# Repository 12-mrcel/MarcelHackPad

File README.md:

# MarcelHackPad
This is the repository for my HackPad Project, which is aptly named "Marcel Hack Pad"
It is a useful hackpad with a rotary encoder, allowing for some extra buttons and functionality when working on my computer.

The design is inspired by the Apollo mission control desks at NASA, I have used several images as inspiration and reference for design choices. This includes: 

1. The color palette (cream and turqouise)
1. The keycap colors 
1. The triangular name plate _"Flight Director"_ (inspired by a real photo!)
1. The NASA logo on a panel on the side

(this is one of the inspirations!)

See it the project here On KiCanvas: 

## Features of the Project:

1. **Six** customizable key switches
2. A Rotary Encoder Switch
3. An opening for a USB-C cable to plug into the microcontroller

### How it works:

I used a Matrix style connection for the key switches, this was because I used 6 or more individual keys and had never designed a matrix-system before. Additionally, the Rotary Encoder Switch is plugged into the microcontroller directly, seperately to the matrix. Next, for the position of the keys and the board, I used the guide provided by HackClub on SandWhich mount keyboards. Finally, I used QMK through HomeBrew to create the firmware of the Keys, which was slightly challenging.

### Acknowledgements:

I used the 3D models provided from these links:

[Key Switches (Cherry MX)](https://github.com/hineybush/CherryMX)

[Rotary Encoder EC11](https://grabcad.com/library/rotary-encoder-17)

[General Resources and Links](https://hackpad.hackclub.com/resources)

Also, I used the HackPad manual:

[HackPad Manual Link](https://hackpad.hackclub.com/)

Finally, I must give credit to two Hackers who provided me with some inspiration and _very_ useful github repos!

[BajajPad by MrKillerShaunBa](https://github.com/MrKillerShaunBa/BajajPad/tree/main)

[HackPad by Ayushj-18](https://github.com/ayushj-18/hackpad/tree/main)

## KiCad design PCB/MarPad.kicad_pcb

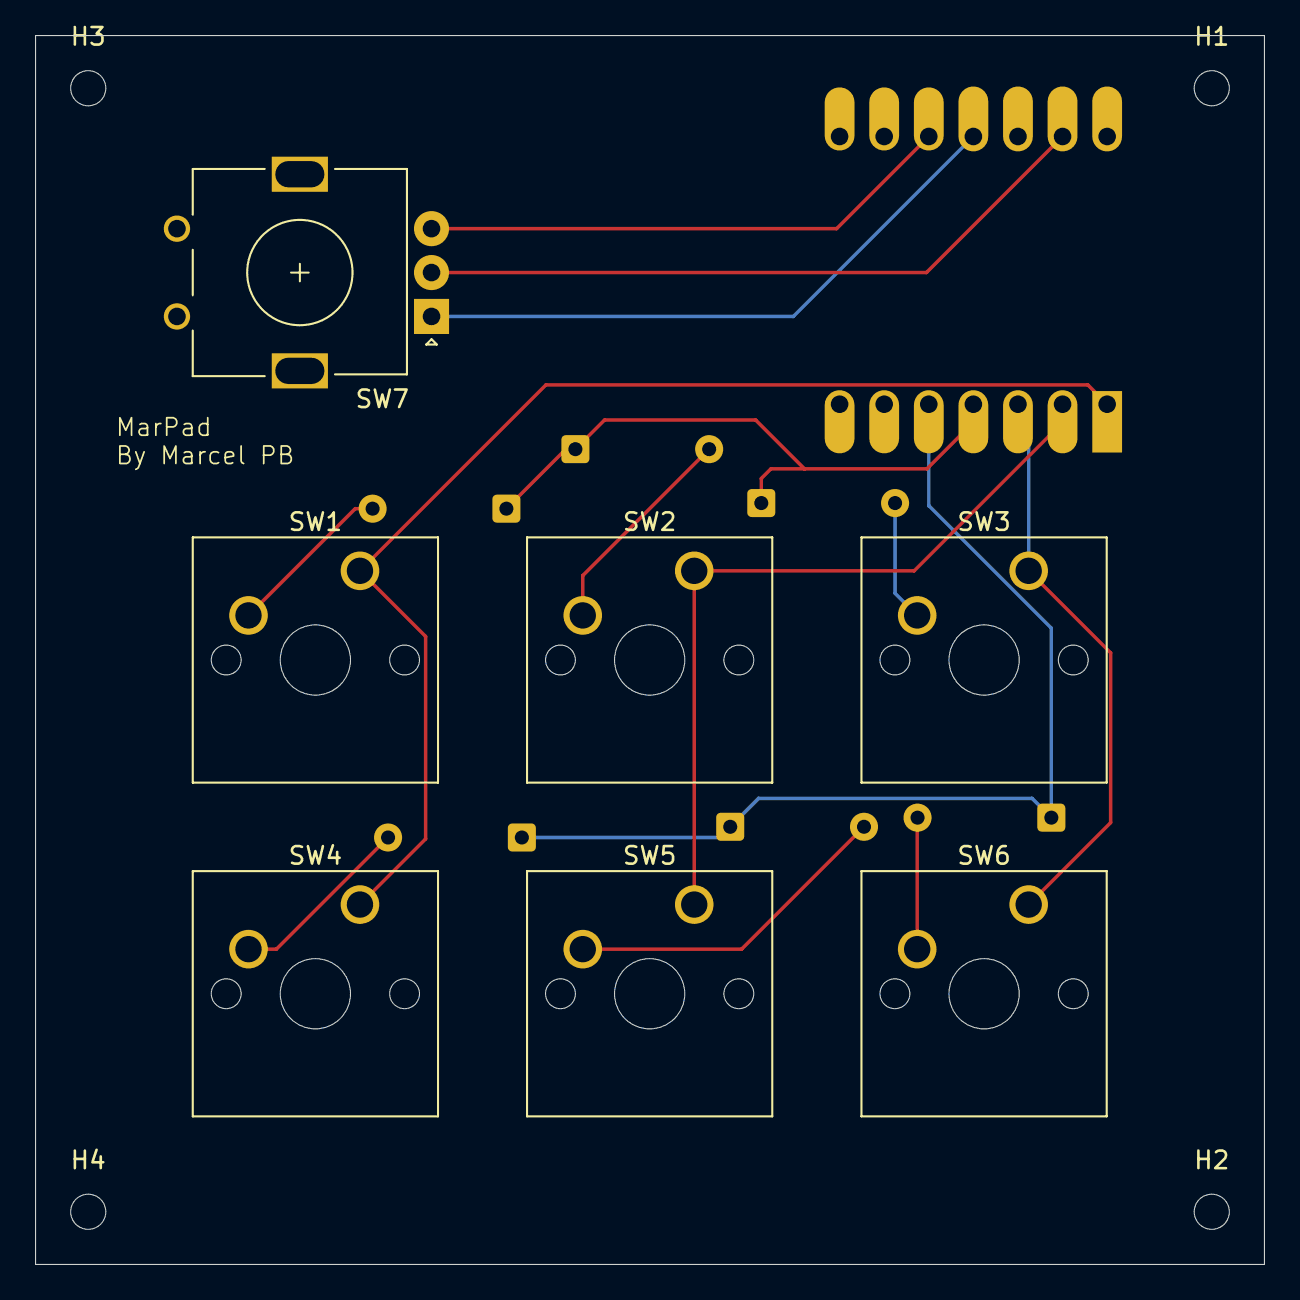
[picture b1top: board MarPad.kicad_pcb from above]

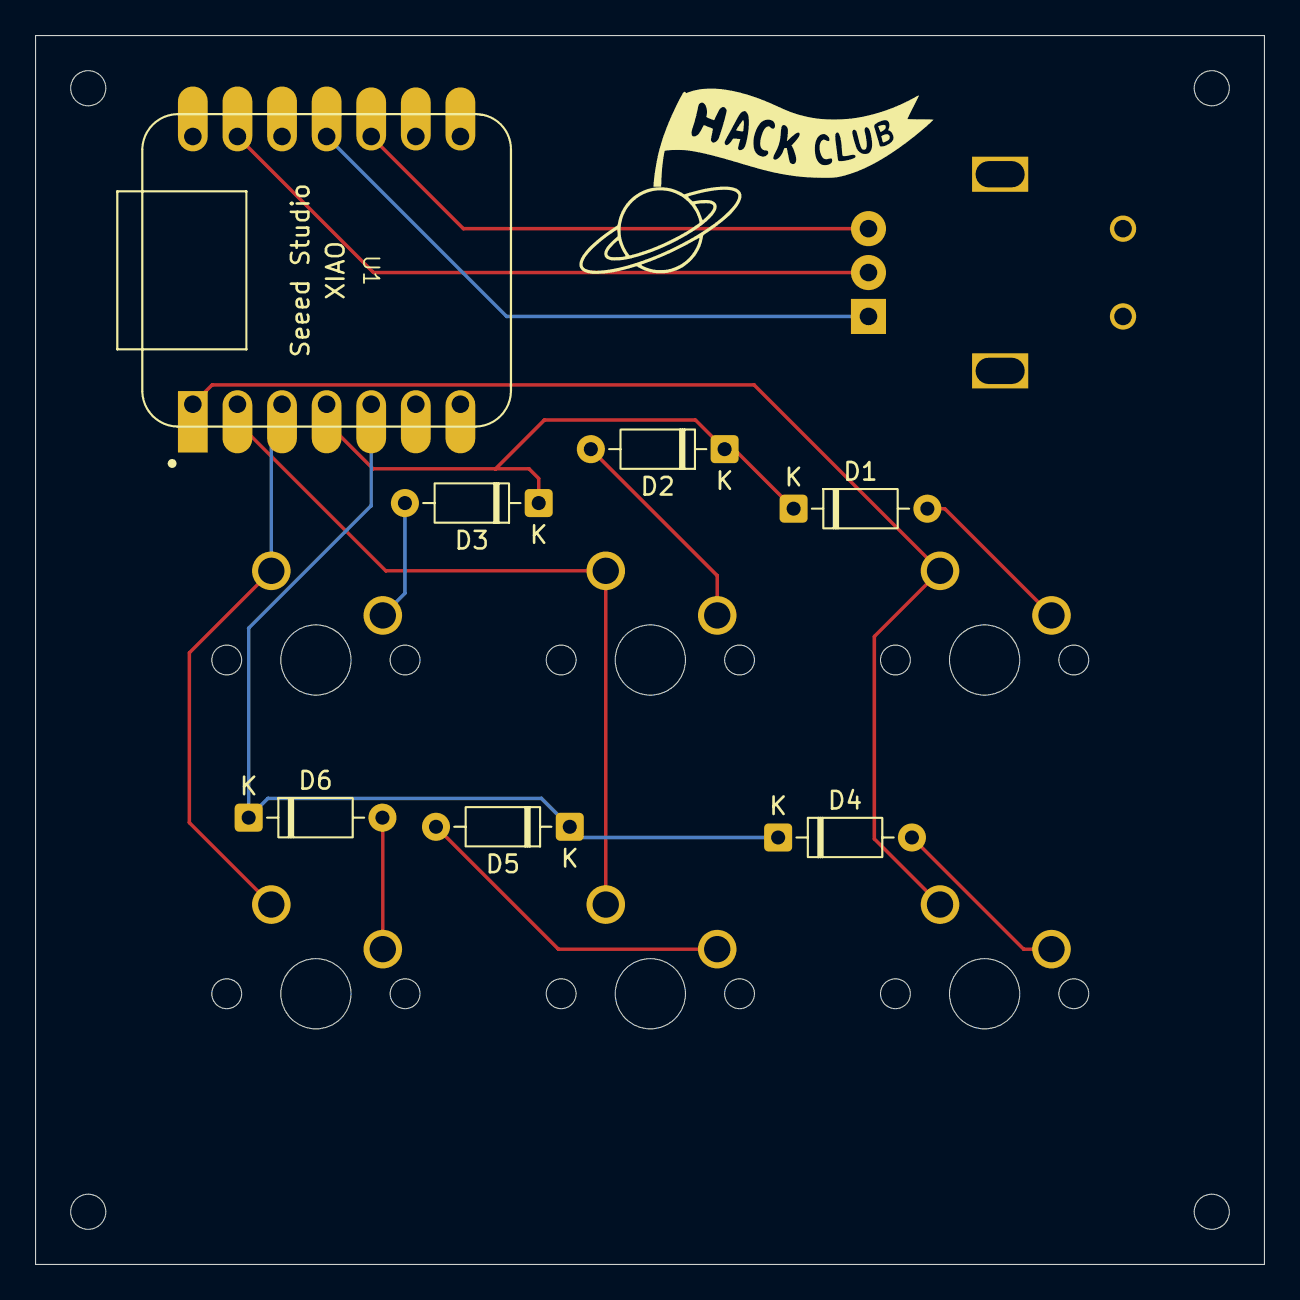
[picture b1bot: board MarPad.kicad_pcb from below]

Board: 2 copper layers, 70.0 x 70.0 mm, 18 parts (7 on the bottom side), 14 nets.

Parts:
D1, D2, D3, D4, D5, D6: 1N4148; D_DO-35_SOD27_P7.62mm_Horizontal
H1, H2, H3, H4: MountingHole; MountingHole_2mm
SW1, SW2, SW3, SW4, SW5, SW6: SW_Push; SW_Cherry_MX_1.00u_PCB
SW7: RotaryEncoder_Switch; RotaryEncoder_Alps_EC11E_Vertical_H20mm
U1: MOUDLE-SEEEDUINO-XIAO; XIAO-Generic-Hybrid-14P-2.54-21X17.8MM

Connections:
Col 0: SW1.1, SW4.1, U1.1 (PA02_A0_D0)
Col 1: SW2.1, SW5.1, U1.2 (PA4_A1_D1)
Col 2: SW3.1, SW6.1, U1.3 (PA10_A2_D2)
GND: SW7.C, U1.13 (GND)
unnamed: D1.2 (A), SW1.2
unnamed: D2.2 (A), SW2.2
unnamed: D3.2 (A), SW3.2
unnamed: D4.2 (A), SW4.2
unnamed: D5.2 (A), SW5.2
unnamed: D6.2 (A), SW6.2
RES A: SW7.A, U1.11 (PA6_A10_D10_MOSI)
RES B: SW7.B, U1.10 (PA5_A9_D9_MISO)
Row 0: D1.1 (K), D2.1 (K), D3.1 (K), U1.4 (PA11_A3_D3)
Row 1: D4.1 (K), D5.1 (K), D6.1 (K), U1.5 (PA8_A4_D4_SDA)

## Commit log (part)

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2026-06-19 Updated README.md for my repo
2026-06-23 Enhance README with project details and features
    Expanded the README with design inspirations and project features.
2026-06-23 Enhance README with project details and acknowledgements
    Added acknowledgements and additional details about the project.
2026-06-23 Update README with acknowledgements and resources
    Added acknowledgements for 3D models and resources used.
2026-06-23 Adding all the files for my Repo
2026-06-23 Create temp
2026-06-23 Uploaded Marpad step files
2026-06-23 Added PCB files
2026-06-23 Keymap upload
2026-06-23 Uploading firmware
2026-06-23 Production files
2026-06-23 Update README with new demo link and image
    Fixed the link for the live demo and added an additional image.
